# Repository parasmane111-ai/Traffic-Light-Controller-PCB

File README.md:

# Traffic Light Controller using 555 Timer, 7490 Counter, 74LS74 and Logic Gates

This project is a **two-way traffic light controller** designed using basic digital electronics ICs.  
The circuit controls the Red, Yellow, and Green signals for two roads, Road A and Road B, in a fixed cyclic sequence.

The main purpose of this project is to understand how **timing, counting, decoding, flip-flop state control, and output logic** can be combined to build a practical digital control system.

---

## Project Overview

In this project, a **555 timer** is used in astable mode to generate continuous clock pulses.  
These clock pulses are applied to a **7490 decade counter**, which is configured as a **MOD-10 counter**.

The MOD-10 counter counts from **0 to 9** and then resets back to 0, creating a repeated timing cycle.  
The output bits of the counter are decoded using logic gates such as **NOT, AND, OR, and XOR gates**.  
These decoded signals are then used with **74LS74 D flip-flops** to control the traffic light states.

Finally, the output logic drives LEDs representing the traffic lights for Road A and Road B.

---

## Working Principle

The working of the circuit can be divided into the following stages:

1. **Clock Generation**

   The 555 timer is configured in astable mode.  
   It produces continuous square wave clock pulses.  
   The timing of these pulses depends on external components such as resistors, capacitors, and diode.

2. **MOD-10 Counting**

   The clock pulses are given to the 7490 counter.  
   The 7490 is configured as a MOD-10 decade counter, so it counts from 0 to 9 repeatedly.  
   This count sequence is used as the timing base for the traffic light operation.

3. **Logic Decoding**

   The counter outputs are connected to logic gates.  
   The combination of 74LS04, 74LS08, 74LS32, and 74LS86 ICs is used to decode specific count conditions.  
   These decoded outputs decide which traffic signal should be ON at a particular state.

4. **State Control**

   The 74LS74 D flip-flop is used for stable state control.  
   It helps in maintaining proper switching between the traffic light states.

5. **Output Indication**

   LEDs are used to represent Red, Yellow, and Green signals for both roads.  
   Current-limiting resistors are connected with LEDs to protect them from excess current.

---

## Traffic Light Sequence

The traffic light controller follows a four-state sequence:

| State | Road A | Road B |
|------|--------|--------|
| S0 | Green | Red |
| S1 | Yellow | Red |
| S2 | Red | Green |
| S3 | Red | Yellow |

After state S3, the sequence returns to S0 and repeats continuously.

---

## Main Components Used

| Component | Purpose |
|----------|---------|
| NE555 Timer | Generates clock pulses in astable mode |
| 7490 Counter | Works as MOD-10 counter for timing sequence |
| 74LS74 D Flip-Flop | Stores and controls logic states |
| 74LS04 NOT Gate | Provides signal inversion |
| 74LS08 AND Gate | Used for logic decoding and gating |
| 74LS32 OR Gate | Combines logic conditions |
| 74LS86 XOR Gate | Used for logic operation and decoding |
| LEDs | Indicate Red, Yellow, and Green signals |
| 220Ω Resistors | Limit LED current |
| R1, R2, C1, C2, D1 | Timing components for 555 timer |

---

## Software and Tools Used

- **Proteus** – Circuit schematic and simulation
- **KiCad** – Schematic design, footprint assignment, PCB layout
- **Digital Logic ICs** – 555, 7490, 74LS74, 74LS04, 74LS08, 74LS32, 74LS86

---

## PCB Design

The PCB layout was designed in KiCad using through-hole components.  
All major ICs and output LEDs are placed in a structured layout for easy understanding and hardware implementation.

Design details:

- 2-layer PCB layout
- Through-hole DIP IC packages
- Separate LED outputs for Road A and Road B
- Current-limiting resistors for each LED
- ERC completed with 0 errors
- Footprints assigned for all components

---

## Folder Structure

```text
Traffic-Light-Controller/
│
├── README.md
│
├── Proteus_Schematic/
│
├── KiCad_PCB/

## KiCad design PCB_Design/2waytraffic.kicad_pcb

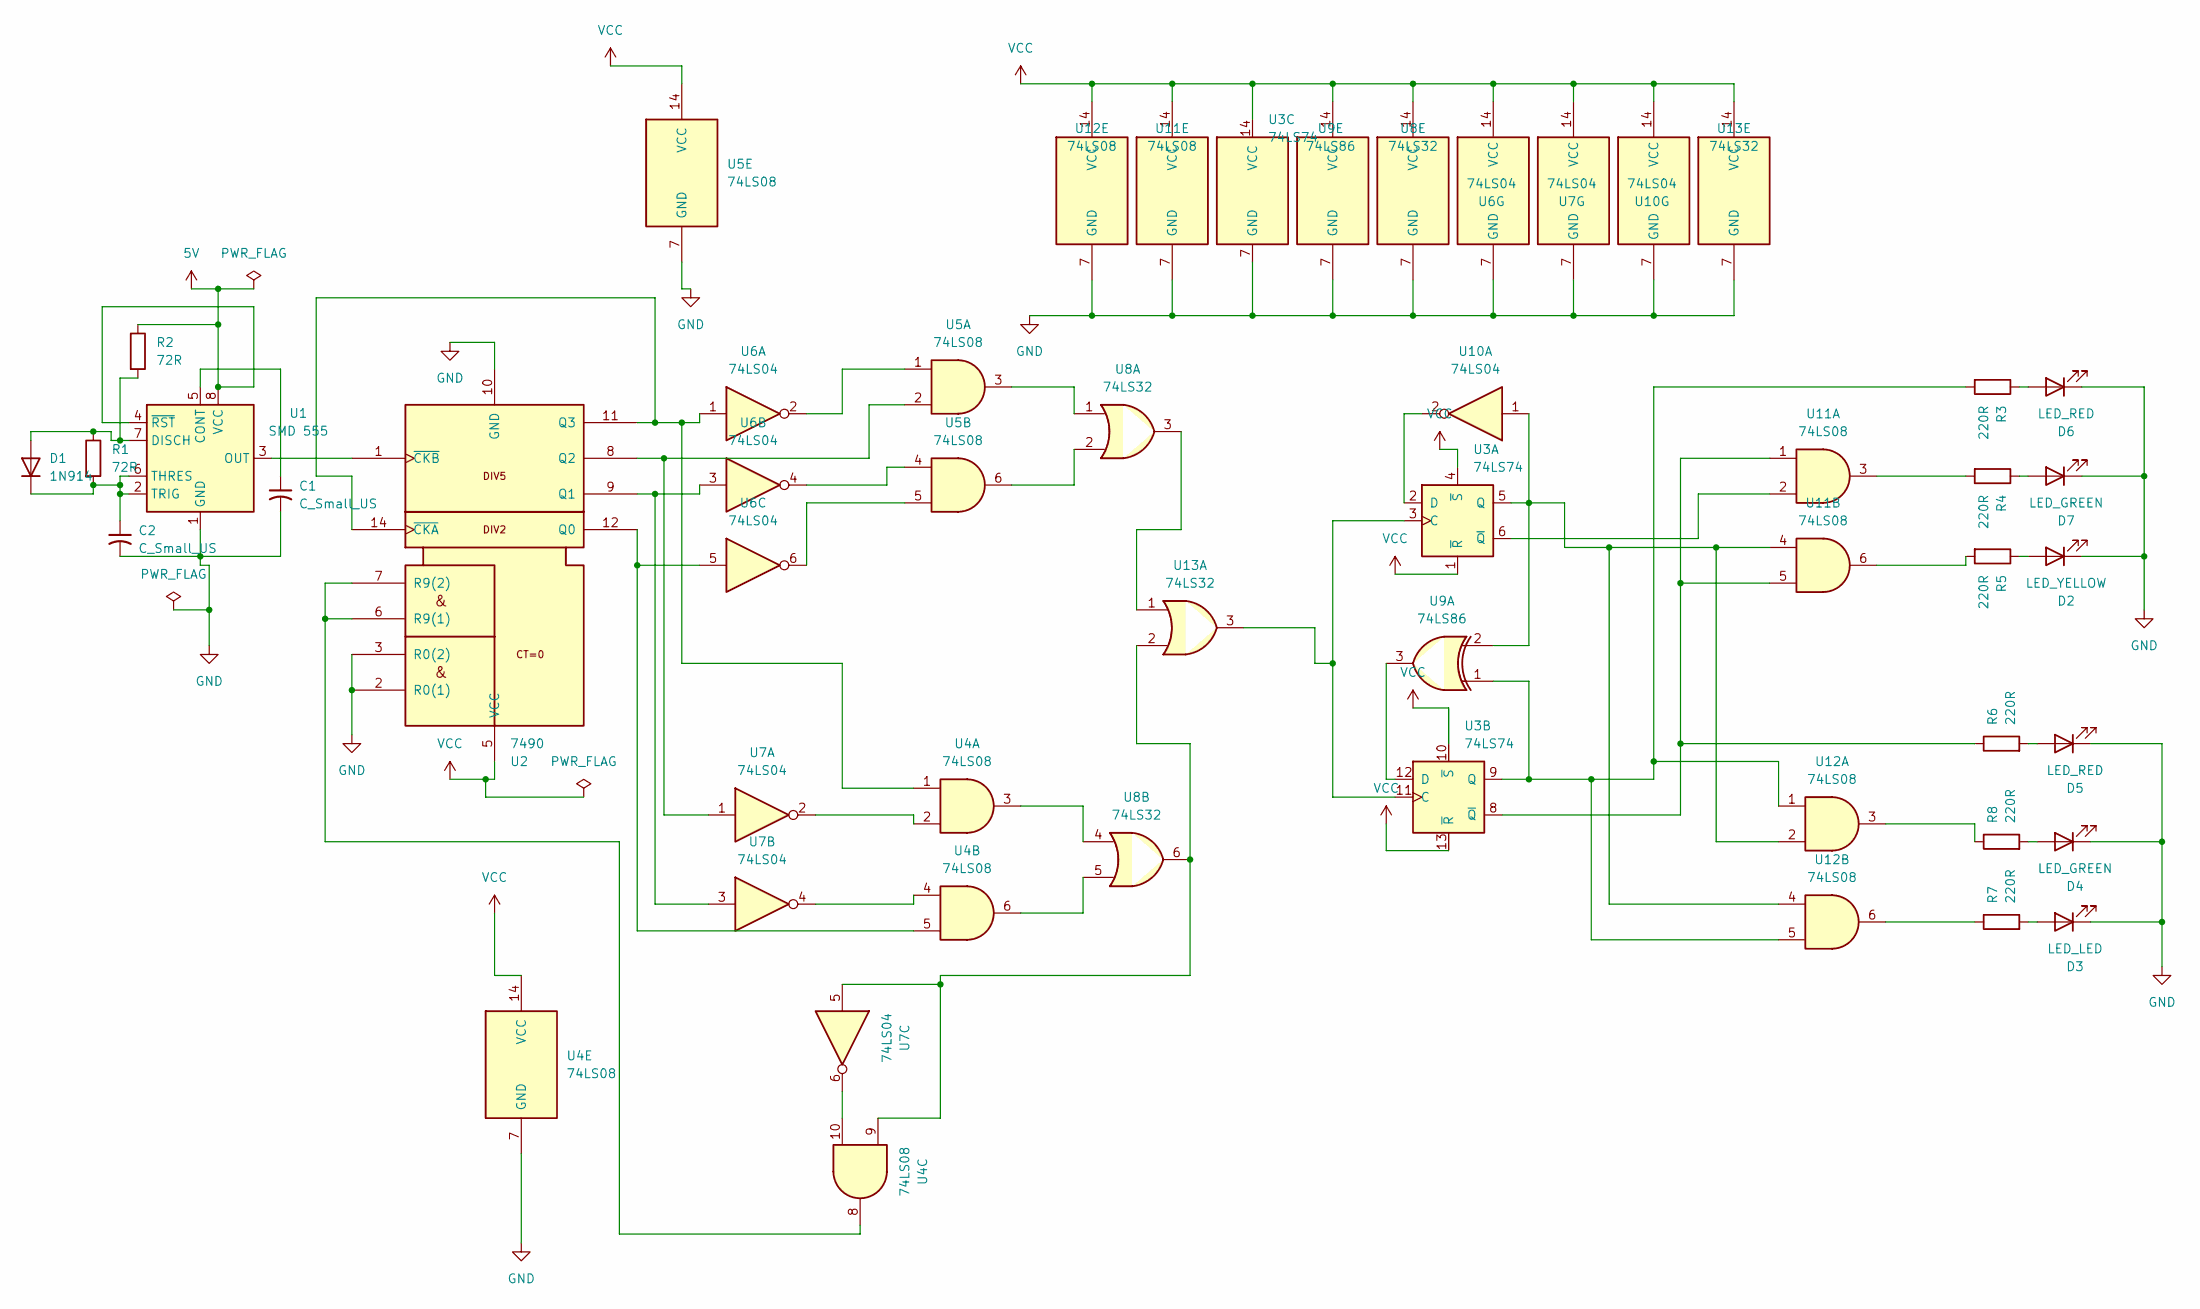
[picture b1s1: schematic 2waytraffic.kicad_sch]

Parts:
C1: C_Small_US; C_Disc_D5.0mm_W2.5mm_P5.00mm
C2: C_Small_US; CP_Radial_D5.0mm_P2.00mm
D1: 1N914; D_DO-35_SOD27_P7.62mm_Horizontal
D2: LED_YELLOW; LED_D5.0mm
D3: LED_LED; LED_D5.0mm
D4, D7: LED_GREEN; LED_D5.0mm
D5, D6: LED_RED; LED_D5.0mm
R1, R2: 72R; R_Axial_DIN0207_L6.3mm_D2.5mm_P7.62mm_Horizontal
R3, R4, R5, R6, R7, R8: 220R; R_Axial_DIN0207_L6.3mm_D2.5mm_P7.62mm_Horizontal
U1: SMD 555; DIP-8-16_W7.62mm
U2: 7490; DIP-14_W7.62mm
U3: 74LS74; DIP-14_W7.62mm
U4, U5, U11, U12: 74LS08; DIP-14_W7.62mm
U6, U7, U10: 74LS04; DIP-14_W7.62mm
U8, U13: 74LS32; DIP-14_W7.62mm
U9: 74LS86; DIP-14_W7.62mm

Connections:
5V: R2.1, U1.4 (~RST), U1.8 (VCC)
GND: C1.2, C2.2, D2.1 (K), D3.1 (K), D4.1 (K), D5.1 (K), D6.1 (K), D7.1 (K), U1.1 (GND), U2.2 (R0(1)), U2.3 (R0(2)), U2.10 (GND), U3.7 (GND), U4.7 (GND), U5.7 (GND), U6.7 (GND), U7.7 (GND), U8.7 (GND), U9.7 (GND), U10.7 (GND), U11.7 (GND), U12.7 (GND), U13.7 (GND)
unnamed: D1.2 (A), R1.1, R2.2, U1.7 (DISCH)
unnamed: C2.1, D1.1 (K), R1.2, U1.2 (TRIG), U1.6 (THRES)
unnamed: D2.2 (A), R5.1
unnamed: D3.2 (A), R7.2
unnamed: D4.2 (A), R8.2
unnamed: D5.2 (A), R6.2
unnamed: D6.2 (A), R3.1
unnamed: D7.2 (A), R4.1
unnamed: R4.2, U11.3
unnamed: R5.2, U11.6
unnamed: R7.1, U12.6
unnamed: R8.1, U12.3
unnamed: C1.1, U1.5 (CONT)
unnamed: U1.3 (OUT), U2.1 (~CKB)
unnamed: U2.12 (Q0), U4.5, U6.5
unnamed: U2.9 (Q1), U6.3, U7.3
unnamed: U2.8 (Q2), U5.2, U7.1
unnamed: U2.11 (Q3), U2.14 (~CKA), U4.1, U6.1
unnamed: U2.6 (R9(1)), U2.7 (R9(2)), U4.8
unnamed: U3.3 (C), U3.11 (C), U13.3
unnamed: U3.2 (D), U10.2
unnamed: U3.5 (Q), U9.2, U10.1, U11.4, U12.2, U12.4
unnamed: U3.6 (~Q), U11.2
unnamed: U3.12 (D), U9.3
unnamed: R3.2, U3.9 (Q), U9.1, U12.1, U12.5
unnamed: R6.1, U3.8 (~Q), U11.1, U11.5
unnamed: U4.2, U7.2
unnamed: U4.3, U8.4
unnamed: U4.4, U7.4
unnamed: U4.6, U8.5
unnamed: U4.10, U7.6
unnamed: U5.1, U6.2
unnamed: U5.3, U8.1
unnamed: U5.4, U6.4
unnamed: U5.5, U6.6
unnamed: U5.6, U8.2
unnamed: U8.3, U13.1
unnamed: U4.9, U7.5, U8.6, U13.2
VCC: U2.5 (VCC), U3.1 (~R), U3.4 (~S), U3.10 (~S), U3.13 (~R), U3.14 (VCC), U4.14 (VCC), U5.14 (VCC), U6.14 (VCC), U7.14 (VCC), U8.14 (VCC), U9.14 (VCC), U10.14 (VCC), U11.14 (VCC), U12.14 (VCC), U13.14 (VCC)

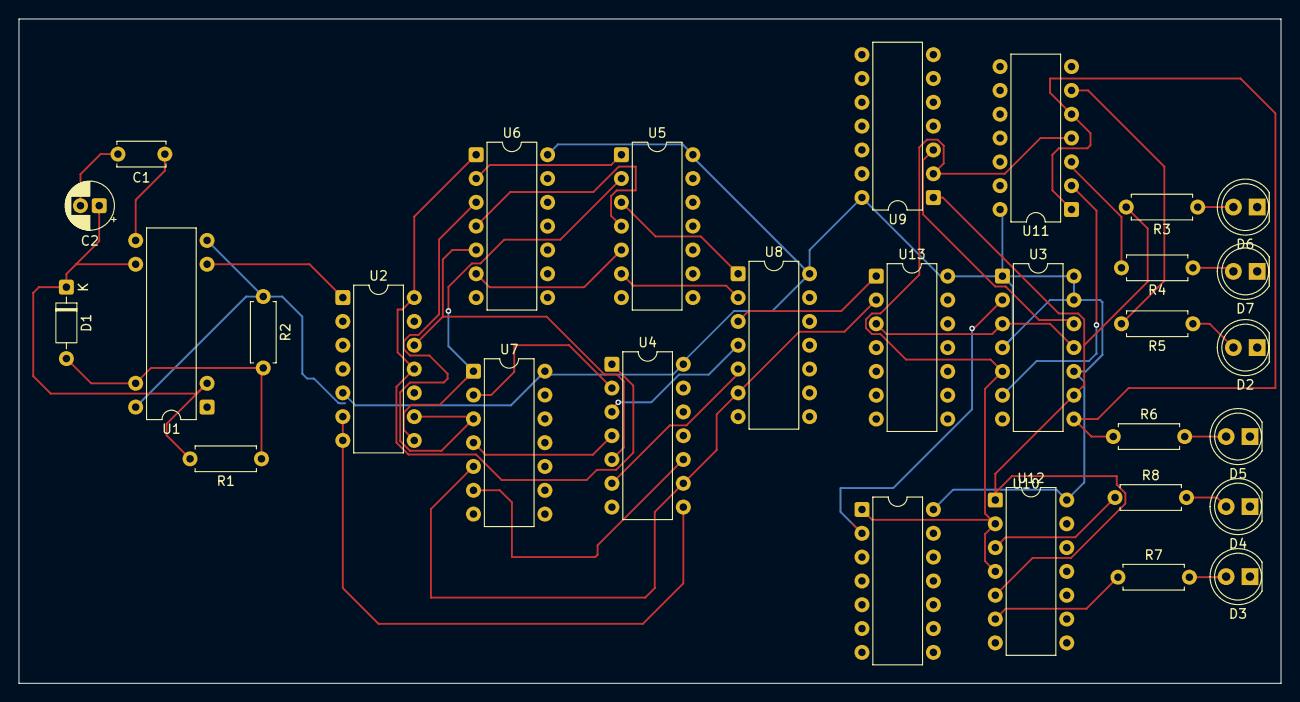
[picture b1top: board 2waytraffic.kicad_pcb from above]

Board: 2 copper layers, 134.6 x 70.9 mm, 30 parts (0 on the bottom side), 41 nets.

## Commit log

2026-06-12 Create tenp
